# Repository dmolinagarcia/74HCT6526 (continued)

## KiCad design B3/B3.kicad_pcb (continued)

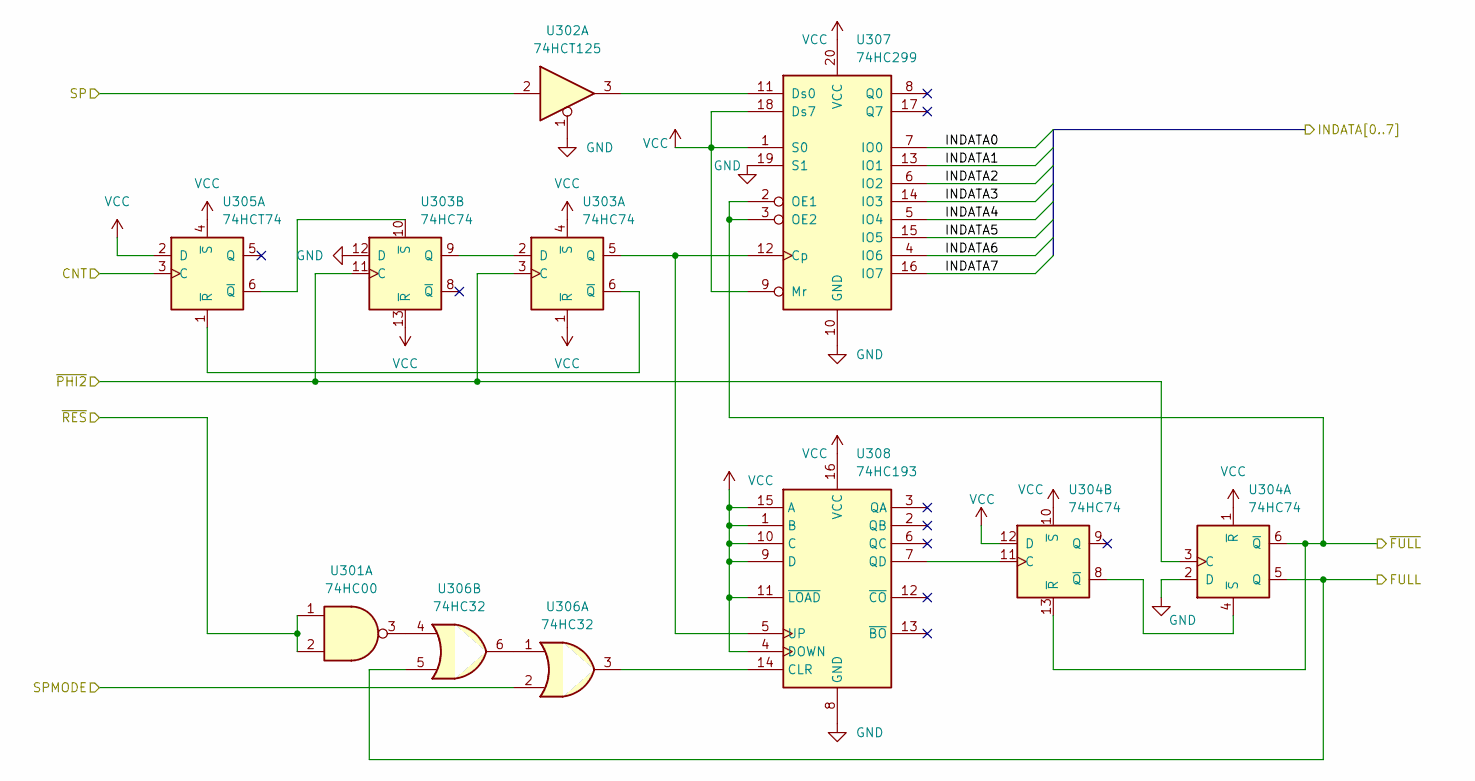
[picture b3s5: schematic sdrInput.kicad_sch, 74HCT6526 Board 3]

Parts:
U301: 74HC00; SO-14_3.9x8.65mm_P1.27mm
U302: 74HCT125; SO-14_3.9x8.65mm_P1.27mm
U303, U304: 74HC74; SO-14_3.9x8.65mm_P1.27mm
U305: 74HCT74; SO-14_3.9x8.65mm_P1.27mm
U306: 74HC32; SO-14_3.9x8.65mm_P1.27mm
U307: 74HC299; SOIC-20W_7.5x12.8mm_P1.27mm
U308: 74HC193; SO-16_3.9x9.9mm_P1.27mm

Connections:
/sdr/sdrController/~FULL: U304.6 (~Q), U304.13 (~R), U307.2 (OE1), U307.3 (OE2); also elsewhere on the board
/sdr/sdrInput/FULL: U304.5 (Q), U306.5; also elsewhere on the board
/sdr/sdrInput/INDATA0: U307.7 (IO0); also elsewhere on the board
/sdr/sdrInput/INDATA1: U307.13 (IO1); also elsewhere on the board
/sdr/sdrInput/INDATA2: U307.6 (IO2); also elsewhere on the board
/sdr/sdrInput/INDATA3: U307.14 (IO3); also elsewhere on the board
/sdr/sdrInput/INDATA4: U307.5 (IO4); also elsewhere on the board
/sdr/sdrInput/INDATA5: U307.15 (IO5); also elsewhere on the board
/sdr/sdrInput/INDATA6: U307.4 (IO6); also elsewhere on the board
/sdr/sdrInput/INDATA7: U307.16 (IO7); also elsewhere on the board
/~PHI2: U303.3 (C), U303.11 (C), U304.3 (C); also elsewhere on the board
CNT: U305.3 (C); also elsewhere on the board
GND: U302.1, U303.12 (D), U304.2 (D), U307.10 (GND), U307.19 (S1), U308.8 (GND); also elsewhere on the board
unnamed: U301.3, U306.4
unnamed: U302.3, U307.11 (Ds0)
unnamed: U303.2 (D), U303.9 (Q)
unnamed: U303.5 (Q), U307.12 (Cp), U308.5 (UP)
unnamed: U303.6 (~Q), U305.1 (~R)
unnamed: U303.10 (~S), U305.6 (~Q)
unnamed: U304.4 (~S), U304.8 (~Q)
unnamed: U304.11 (C), U308.7 (QD)
unnamed: U306.1, U306.6
unnamed: U306.3, U308.14 (CLR)
SP: U302.2; also elsewhere on the board
SPMODE: U306.2; also elsewhere on the board
VCC: U303.1 (~R), U303.4 (~S), U303.13 (~R), U304.1 (~R), U304.10 (~S), U304.12 (D), U305.2 (D), U305.4 (~S), U307.1 (S0), U307.9 (Mr), U307.18 (Ds7), U307.20 (VCC), U308.1 (B), U308.4 (DOWN), U308.9 (D), U308.10 (C), U308.11 (~LOAD), U308.15 (A), U308.16 (VCC); also elsewhere on the board
~RES: U301.1, U301.2; also elsewhere on the board

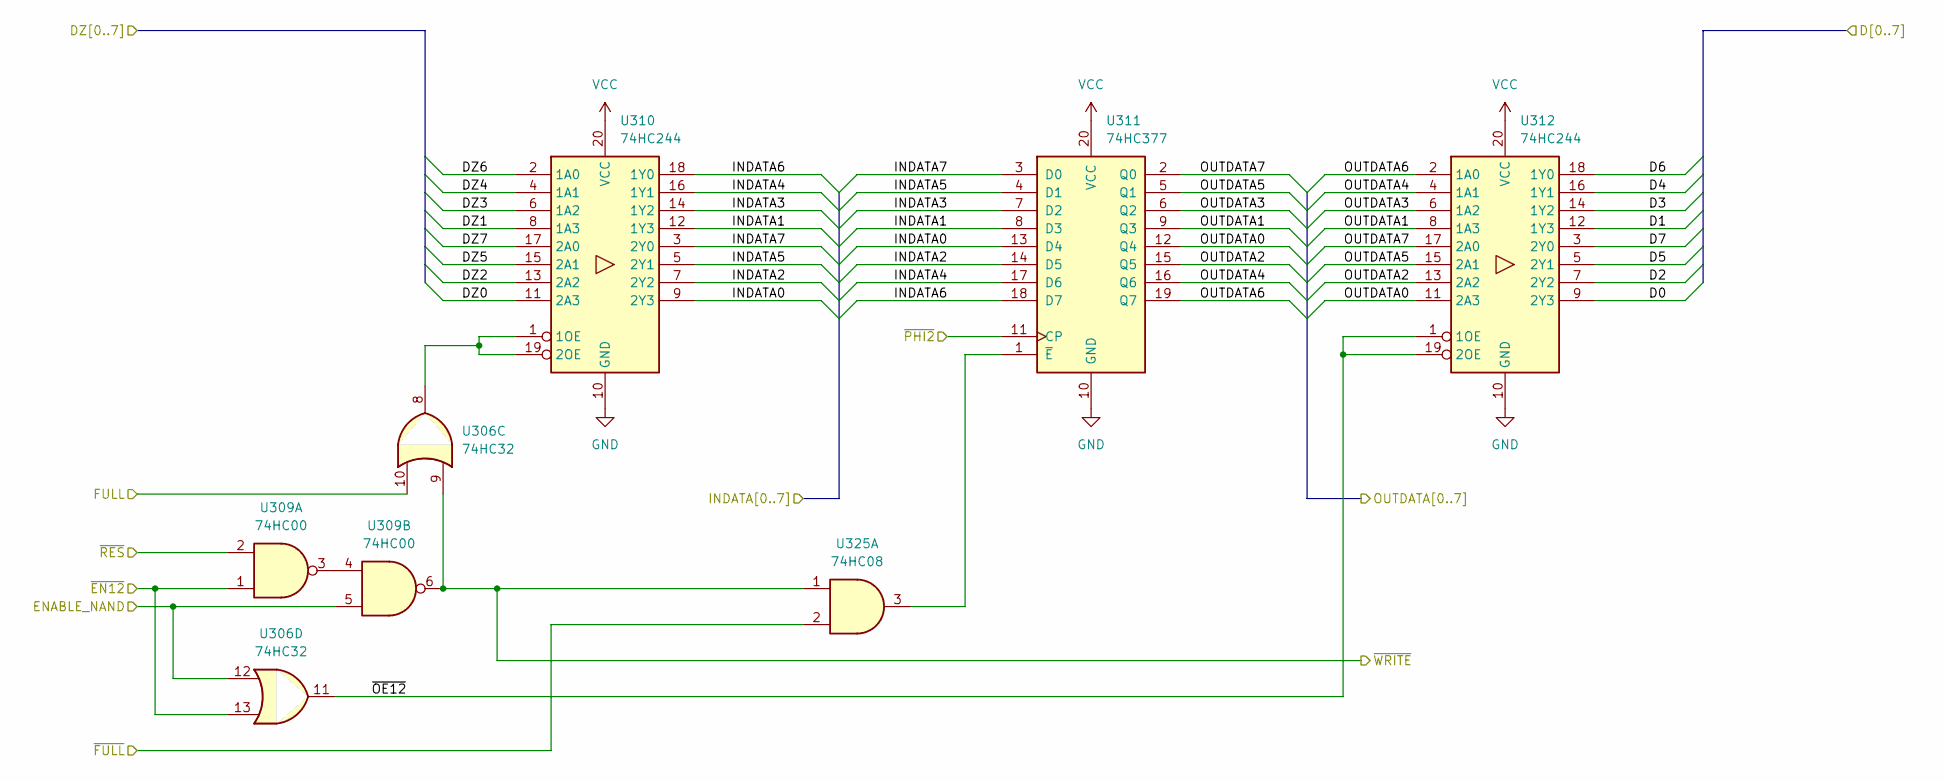
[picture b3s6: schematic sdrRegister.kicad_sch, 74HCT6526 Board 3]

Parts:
U306: 74HC32; SO-14_3.9x8.65mm_P1.27mm
U309: 74HC00; SO-14_3.9x8.65mm_P1.27mm
U310, U312: 74HC244; SOIC-20W_7.5x12.8mm_P1.27mm
U311: 74HC377; SOIC-20W_7.5x12.8mm_P1.27mm
U325: 74HC08; SO-14_3.9x8.65mm_P1.27mm

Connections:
/sdr/sdrController/~FULL: U325.2; also elsewhere on the board
/sdr/sdrController/~WRITE: U306.9, U309.6, U325.1; also elsewhere on the board
/sdr/sdrInput/FULL: U306.10; also elsewhere on the board
/sdr/sdrInput/INDATA0: U310.9 (2Y3), U311.13 (D4); also elsewhere on the board
/sdr/sdrInput/INDATA1: U310.12 (1Y3), U311.8 (D3); also elsewhere on the board
/sdr/sdrInput/INDATA2: U310.7 (2Y2), U311.14 (D5); also elsewhere on the board
/sdr/sdrInput/INDATA3: U310.14 (1Y2), U311.7 (D2); also elsewhere on the board
/sdr/sdrInput/INDATA4: U310.16 (1Y1), U311.17 (D6); also elsewhere on the board
/sdr/sdrInput/INDATA5: U310.5 (2Y1), U311.4 (D1); also elsewhere on the board
/sdr/sdrInput/INDATA6: U310.18 (1Y0), U311.18 (D7); also elsewhere on the board
/sdr/sdrInput/INDATA7: U310.3 (2Y0), U311.3 (D0); also elsewhere on the board
/sdr/sdrOutput/OUTDATA0: U311.12 (Q4), U312.11 (2A3); also elsewhere on the board
/sdr/sdrOutput/OUTDATA1: U311.9 (Q3), U312.8 (1A3); also elsewhere on the board
/sdr/sdrOutput/OUTDATA2: U311.15 (Q5), U312.13 (2A2); also elsewhere on the board
/sdr/sdrOutput/OUTDATA3: U311.6 (Q2), U312.6 (1A2); also elsewhere on the board
/sdr/sdrOutput/OUTDATA4: U311.16 (Q6), U312.4 (1A1); also elsewhere on the board
/sdr/sdrOutput/OUTDATA5: U311.5 (Q1), U312.15 (2A1); also elsewhere on the board
/sdr/sdrOutput/OUTDATA6: U311.19 (Q7), U312.2 (1A0); also elsewhere on the board
/sdr/sdrOutput/OUTDATA7: U311.2 (Q0), U312.17 (2A0); also elsewhere on the board
/sdr/sdrRegister/~OE12: U306.11, U312.1 (1OE), U312.19 (2OE)
/~PHI2: U311.11 (CP); also elsewhere on the board
D0: U312.9 (2Y3); also elsewhere on the board
D1: U312.12 (1Y3); also elsewhere on the board
D2: U312.7 (2Y2); also elsewhere on the board
D3: U312.14 (1Y2); also elsewhere on the board
D4: U312.16 (1Y1); also elsewhere on the board
D5: U312.5 (2Y1); also elsewhere on the board
D6: U312.18 (1Y0); also elsewhere on the board
D7: U312.3 (2Y0); also elsewhere on the board
DZ0: U310.11 (2A3); also elsewhere on the board
DZ1: U310.8 (1A3); also elsewhere on the board
DZ2: U310.13 (2A2); also elsewhere on the board
DZ3: U310.6 (1A2); also elsewhere on the board
DZ4: U310.4 (1A1); also elsewhere on the board
DZ5: U310.15 (2A1); also elsewhere on the board
DZ6: U310.2 (1A0); also elsewhere on the board
DZ7: U310.17 (2A0); also elsewhere on the board
ENABLE_NAND: U306.12, U309.5; also elsewhere on the board
GND: U310.10 (GND), U311.10 (GND), U312.10 (GND); also elsewhere on the board
unnamed: U306.8, U310.1 (1OE), U310.19 (2OE)
unnamed: U309.3, U309.4
unnamed: U311.1 (~E), U325.3
VCC: U310.20 (VCC), U311.20 (VCC), U312.20 (VCC); also elsewhere on the board
~EN12: U306.13, U309.1; also elsewhere on the board
~RES: U309.2; also elsewhere on the board

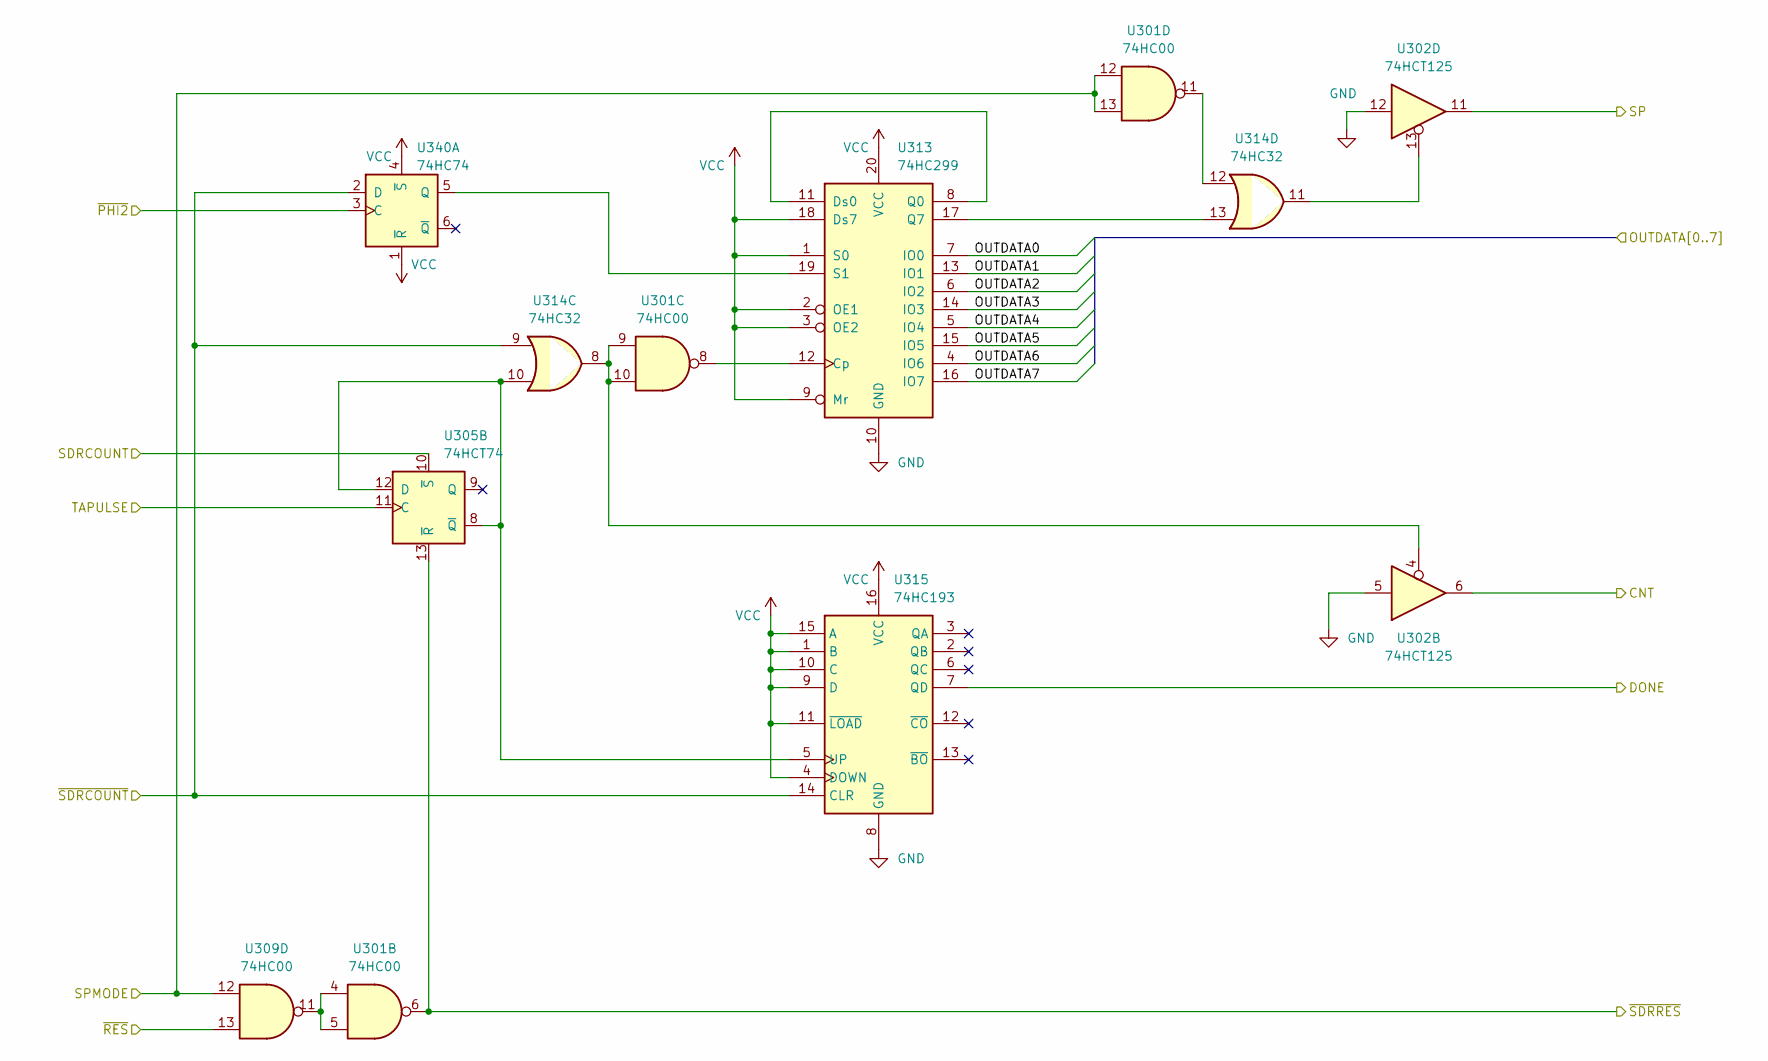
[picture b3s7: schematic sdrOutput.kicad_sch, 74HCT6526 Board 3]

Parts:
U301, U309: 74HC00; SO-14_3.9x8.65mm_P1.27mm
U302: 74HCT125; SO-14_3.9x8.65mm_P1.27mm
U305: 74HCT74; SO-14_3.9x8.65mm_P1.27mm
U313: 74HC299; SOIC-20W_7.5x12.8mm_P1.27mm
U314: 74HC32; SO-14_3.9x8.65mm_P1.27mm
U315: 74HC193; SO-16_3.9x9.9mm_P1.27mm
U340: 74HC74; SO-14_3.9x8.65mm_P1.27mm

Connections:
/sdr/sdrController/DONE: U315.7 (QD); also elsewhere on the board
/sdr/sdrController/SDRCOUNT: U305.10 (~S); also elsewhere on the board
/sdr/sdrController/~SDRCOUNT: U314.9, U315.14 (CLR), U340.2 (D); also elsewhere on the board
/sdr/sdrController/~SDRRES: U301.6, U305.13 (~R); also elsewhere on the board
/sdr/sdrOutput/OUTDATA0: U313.7 (IO0); also elsewhere on the board
/sdr/sdrOutput/OUTDATA1: U313.13 (IO1); also elsewhere on the board
/sdr/sdrOutput/OUTDATA2: U313.6 (IO2); also elsewhere on the board
/sdr/sdrOutput/OUTDATA3: U313.14 (IO3); also elsewhere on the board
/sdr/sdrOutput/OUTDATA4: U313.5 (IO4); also elsewhere on the board
/sdr/sdrOutput/OUTDATA5: U313.15 (IO5); also elsewhere on the board
/sdr/sdrOutput/OUTDATA6: U313.4 (IO6); also elsewhere on the board
/sdr/sdrOutput/OUTDATA7: U313.16 (IO7); also elsewhere on the board
/~PHI2: U340.3 (C); also elsewhere on the board
CNT: U302.6; also elsewhere on the board
GND: U302.5, U302.12, U313.10 (GND), U315.8 (GND); also elsewhere on the board
unnamed: U301.4, U301.5, U309.11
unnamed: U301.8, U313.12 (Cp)
unnamed: U301.9, U301.10, U302.4, U314.8
unnamed: U301.11, U314.12
unnamed: U302.13, U314.11
unnamed: U305.8 (~Q), U305.12 (D), U314.10, U315.5 (UP)
unnamed: U313.8 (Q0), U313.11 (Ds0)
unnamed: U313.17 (Q7), U314.13
unnamed: U313.19 (S1), U340.5 (Q)
SP: U302.11; also elsewhere on the board
SPMODE: U301.12, U301.13, U309.12; also elsewhere on the board
TAPULSE: U305.11 (C); also elsewhere on the board
VCC: U313.1 (S0), U313.2 (OE1), U313.3 (OE2), U313.9 (Mr), U313.18 (Ds7), U313.20 (VCC), U315.1 (B), U315.4 (DOWN), U315.9 (D), U315.10 (C), U315.11 (~LOAD), U315.15 (A), U315.16 (VCC), U340.1 (~R), U340.4 (~S); also elsewhere on the board
~RES: U309.13; also elsewhere on the board

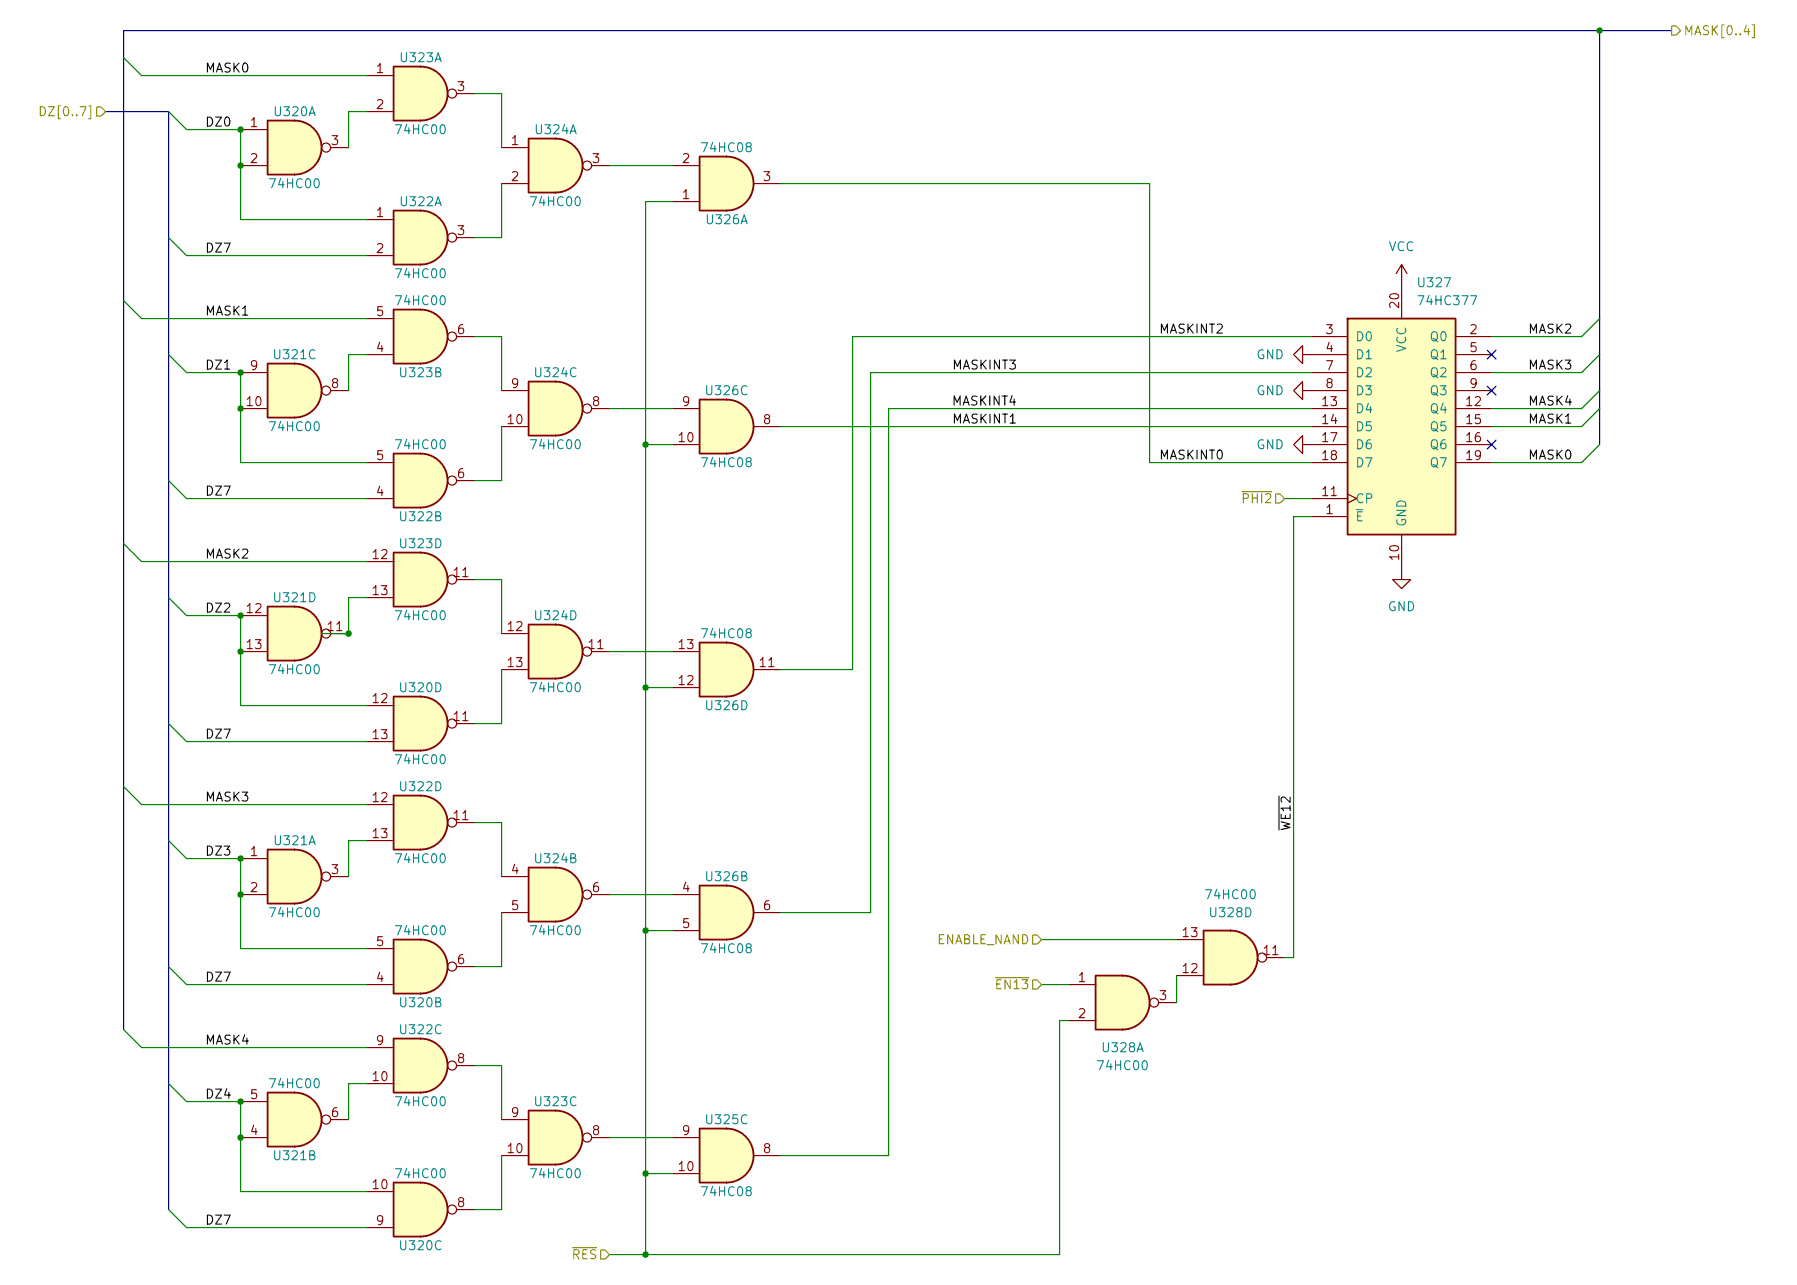
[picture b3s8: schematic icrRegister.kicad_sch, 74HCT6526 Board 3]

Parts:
U320, U321, U322, U323, U324, U328: 74HC00; SO-14_3.9x8.65mm_P1.27mm
U325, U326: 74HC08; SO-14_3.9x8.65mm_P1.27mm
U327: 74HC377; SOIC-20W_7.5x12.8mm_P1.27mm

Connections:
/icr/icrControl/MASK0: U323.1, U327.19 (Q7); also elsewhere on the board
/icr/icrControl/MASK1: U323.5, U327.15 (Q5); also elsewhere on the board
/icr/icrControl/MASK2: U323.12, U327.2 (Q0); also elsewhere on the board
/icr/icrControl/MASK3: U322.12, U327.6 (Q2); also elsewhere on the board
/icr/icrControl/MASK4: U322.9, U327.12 (Q4); also elsewhere on the board
/icr/icrRegister/MASKINT0: U326.3, U327.18 (D7)
/icr/icrRegister/MASKINT1: U326.8, U327.14 (D5)
/icr/icrRegister/MASKINT2: U326.11, U327.3 (D0)
/icr/icrRegister/MASKINT3: U326.6, U327.7 (D2)
/icr/icrRegister/MASKINT4: U325.8, U327.13 (D4)
/icr/icrRegister/~WE12: U327.1 (~E), U328.11
/~PHI2: U327.11 (CP); also elsewhere on the board
DZ0: U320.1, U320.2, U322.1; also elsewhere on the board
DZ1: U321.9, U321.10, U322.5; also elsewhere on the board
DZ2: U320.12, U321.12, U321.13; also elsewhere on the board
DZ3: U320.5, U321.1, U321.2; also elsewhere on the board
DZ4: U320.10, U321.4, U321.5; also elsewhere on the board
DZ7: U320.4, U320.9, U320.13, U322.2, U322.4; also elsewhere on the board
ENABLE_NAND: U328.13; also elsewhere on the board
GND: U327.4 (D1), U327.8 (D3), U327.10 (GND), U327.17 (D6); also elsewhere on the board
unnamed: U320.3, U323.2
unnamed: U320.6, U324.5
unnamed: U320.8, U323.10
unnamed: U320.11, U324.13
unnamed: U321.3, U322.13
unnamed: U321.6, U322.10
unnamed: U321.8, U323.4
unnamed: U321.11, U323.13
unnamed: U322.3, U324.2
unnamed: U322.6, U324.10
unnamed: U322.8, U323.9
unnamed: U322.11, U324.4
unnamed: U323.3, U324.1
unnamed: U323.6, U324.9
unnamed: U323.8, U325.9
unnamed: U323.11, U324.12
unnamed: U324.3, U326.2
unnamed: U324.6, U326.4
unnamed: U324.8, U326.9
unnamed: U324.11, U326.13
unnamed: U328.3, U328.12
VCC: U327.20 (VCC); also elsewhere on the board
~EN13: U328.1; also elsewhere on the board
~RES: U325.10, U326.1, U326.5, U326.10, U326.12, U328.2; also elsewhere on the board

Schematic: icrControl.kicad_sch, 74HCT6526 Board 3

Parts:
SW301: SW_SPDT; SW_SPDT_PCM12
U329: 74HC00; SO-14_3.9x8.65mm_P1.27mm
U330, U331, U332, U333, U334, U342: 74HC74; SO-14_3.9x8.65mm_P1.27mm
U335: 74HCT04; SO-14_3.9x8.65mm_P1.27mm
U336: 74HC244; SOIC-20W_7.5x12.8mm_P1.27mm
U337, U339: 74HC08; SO-14_3.9x8.65mm_P1.27mm
U338: 74HC32; SO-14_3.9x8.65mm_P1.27mm
U341: 74HC157; SO-16_3.9x9.9mm_P1.27mm

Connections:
/icr/icrControl/ICR0: U331.5 (Q), U336.2 (1A0), U339.12
/icr/icrControl/ICR1: U332.9 (Q), U336.17 (2A0)
/icr/icrControl/ICR2: U332.5 (Q), U336.4 (1A1), U337.4
/icr/icrControl/ICR3: U331.9 (Q), U336.15 (2A1), U337.9
/icr/icrControl/ICR4: U333.9 (Q), U336.13 (2A2), U339.9
/icr/icrControl/ICR7: U336.8 (1A3), U341.7
/icr/icrControl/ICRCLR: U329.6, U330.12 (D)
/icr/icrControl/MASK0: U339.13; also elsewhere on the board
/icr/icrControl/MASK1: U337.13; also elsewhere on the board
/icr/icrControl/MASK2: U337.5; also elsewhere on the board
/icr/icrControl/MASK3: U337.10; also elsewhere on the board
/icr/icrControl/MASK4: U339.10; also elsewhere on the board
/icr/icrControl/~ICRCLR1: U330.8 (~Q), U331.1 (~R), U331.13 (~R), U332.1 (~R), U333.13 (~R), U334.1 (~R), U334.13 (~R), U341.2, U342.1 (~R), U342.13 (~R)
/icr/icrControl/~ICRCLR2: U330.6 (~Q), U341.3
/icr/icrControl/~OE13: U329.5, U329.8, U336.1 (1OE), U336.19 (2OE)
/~PHI2: U330.3 (C), U330.11 (C), U334.11 (C), U342.11 (C); also elsewhere on the board
/~SDRIRQ: U331.10 (~S); also elsewhere on the board
D0: U336.18 (1Y0); also elsewhere on the board
D1: U336.3 (2Y0); also elsewhere on the board
D2: U336.16 (1Y1); also elsewhere on the board
D3: U336.5 (2Y1); also elsewhere on the board
D4: U336.7 (2Y2); also elsewhere on the board
D5: U336.14 (1Y2); also elsewhere on the board
D6: U336.9 (2Y3); also elsewhere on the board
D7: U336.12 (1Y3); also elsewhere on the board
ENABLE_NAND: U329.12, U329.13; also elsewhere on the board
GND: SW301.1 (A), U336.6 (1A2), U336.10 (GND), U336.11 (2A3), U341.15 (~E); also elsewhere on the board
unnamed: SW301.2 (B), U341.1 (S)
unnamed: U329.3, U329.9
unnamed: U329.10, U329.11
unnamed: U330.2 (D), U330.9 (Q)
unnamed: U331.4 (~S), U335.10
unnamed: U332.4 (~S), U335.2
unnamed: U332.10 (~S), U335.12
unnamed: U332.13 (~R), U341.4
unnamed: U333.1 (~R), U333.8 (~Q)
unnamed: U333.3 (C), U335.4
unnamed: U333.6 (~Q), U333.10 (~S)
unnamed: U334.4 (~S), U335.8, U342.4 (~S)
unnamed: U334.9 (Q), U341.6
unnamed: U334.5 (Q), U334.12 (D), U341.5
unnamed: U335.9, U338.6
unnamed: U337.6, U338.12
unnamed: U337.8, U338.13
unnamed: U337.11, U338.2
unnamed: U338.1, U339.11
unnamed: U338.3, U338.9
unnamed: U338.4, U338.8
unnamed: U338.5, U339.8
unnamed: U338.10, U338.11
unnamed: U341.10, U342.8 (~Q)
unnamed: U341.11, U342.6 (~Q)
unnamed: U342.5 (Q), U342.12 (D)
TAPULSE: U335.11; also elsewhere on the board
TBPULSE: U335.13, U337.12; also elsewhere on the board
TODIRQ: U335.1; also elsewhere on the board
VCC: SW301.3 (C), U330.1 (~R), U330.4 (~S), U330.10 (~S), U330.13 (~R), U331.2 (D), U331.3 (C), U331.11 (C), U331.12 (D), U332.2 (D), U332.3 (C), U332.11 (C), U332.12 (D), U333.2 (D), U333.4 (~S), U333.11 (C), U333.12 (D), U334.2 (D), U334.3 (C), U334.10 (~S), U336.20 (VCC), U342.2 (D), U342.3 (C), U342.10 (~S); also elsewhere on the board
~EN13: U329.1, U329.2; also elsewhere on the board
~FLAG: U335.3; also elsewhere on the board
~IRQ: U341.9; also elsewhere on the board
~RES: U329.4; also elsewhere on the board

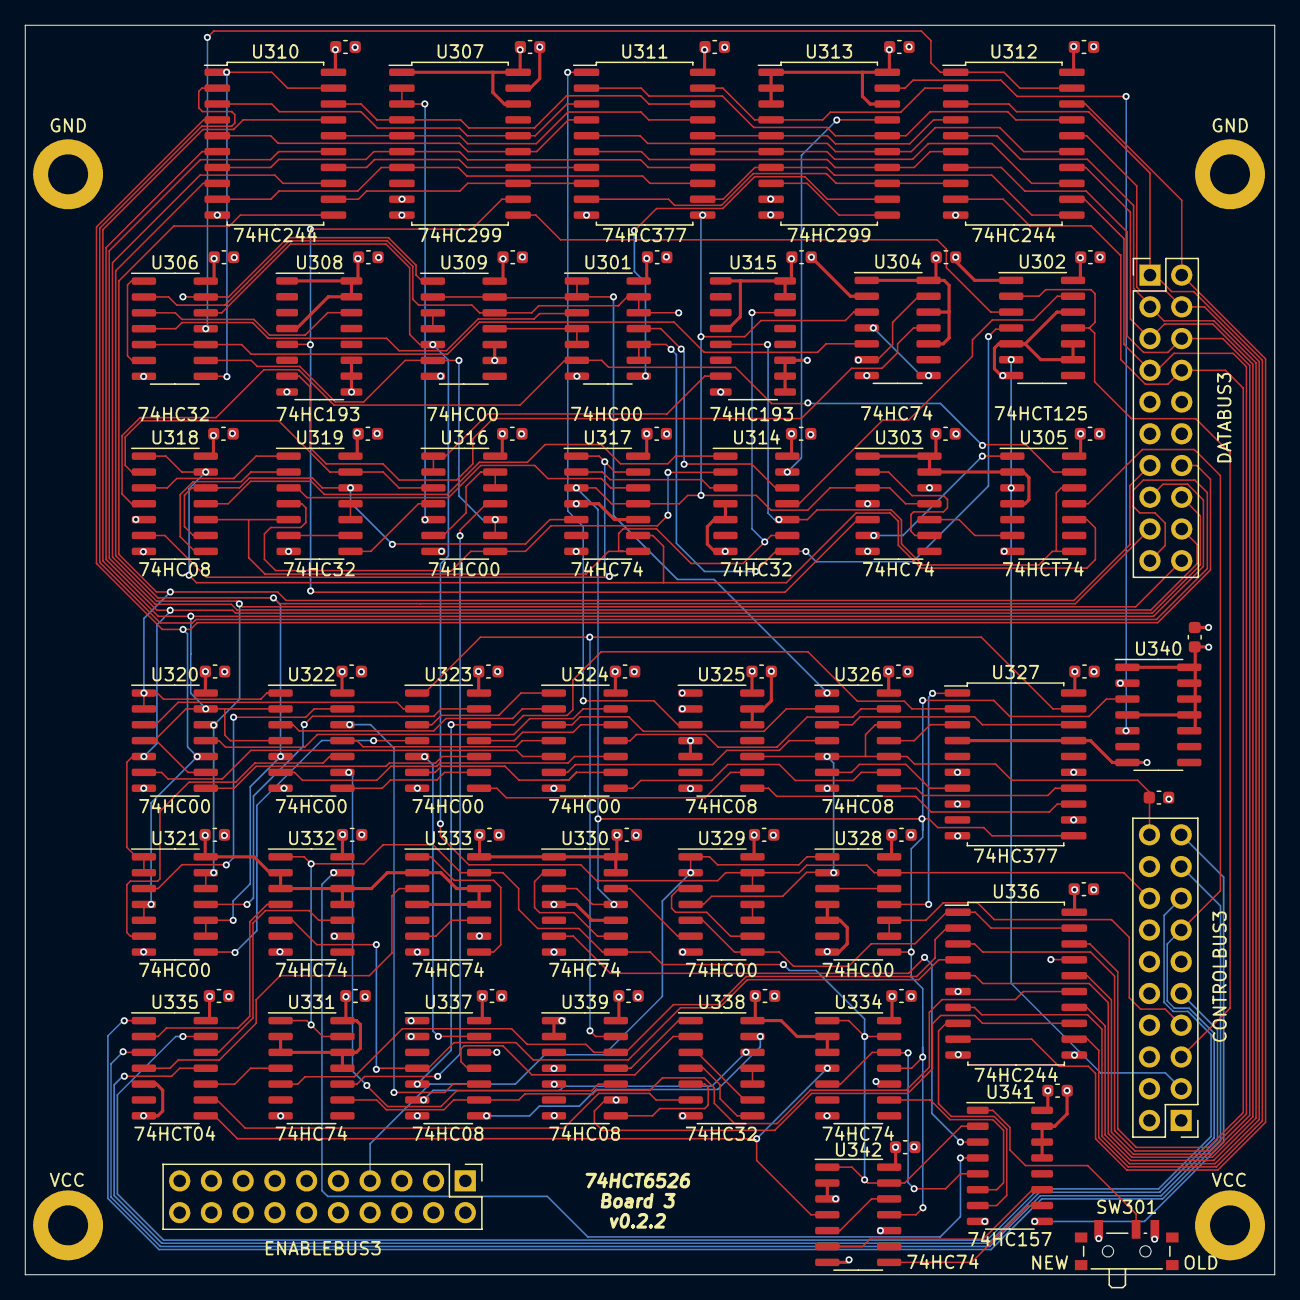
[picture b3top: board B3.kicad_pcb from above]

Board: 4 copper layers, 100.0 x 100.0 mm, 93 parts (0 on the bottom side), 161 nets.

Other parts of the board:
GND101, GND102: GND; MountingHole_2.2mm_M2_DIN965_Pad
VCC101, VCC102: VCC; MountingHole_2.2mm_M2_DIN965_Pad

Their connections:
GND: GND101.GND, GND102.GND; also elsewhere on the board
VCC: VCC101.VCC, VCC102.VCC; also elsewhere on the board

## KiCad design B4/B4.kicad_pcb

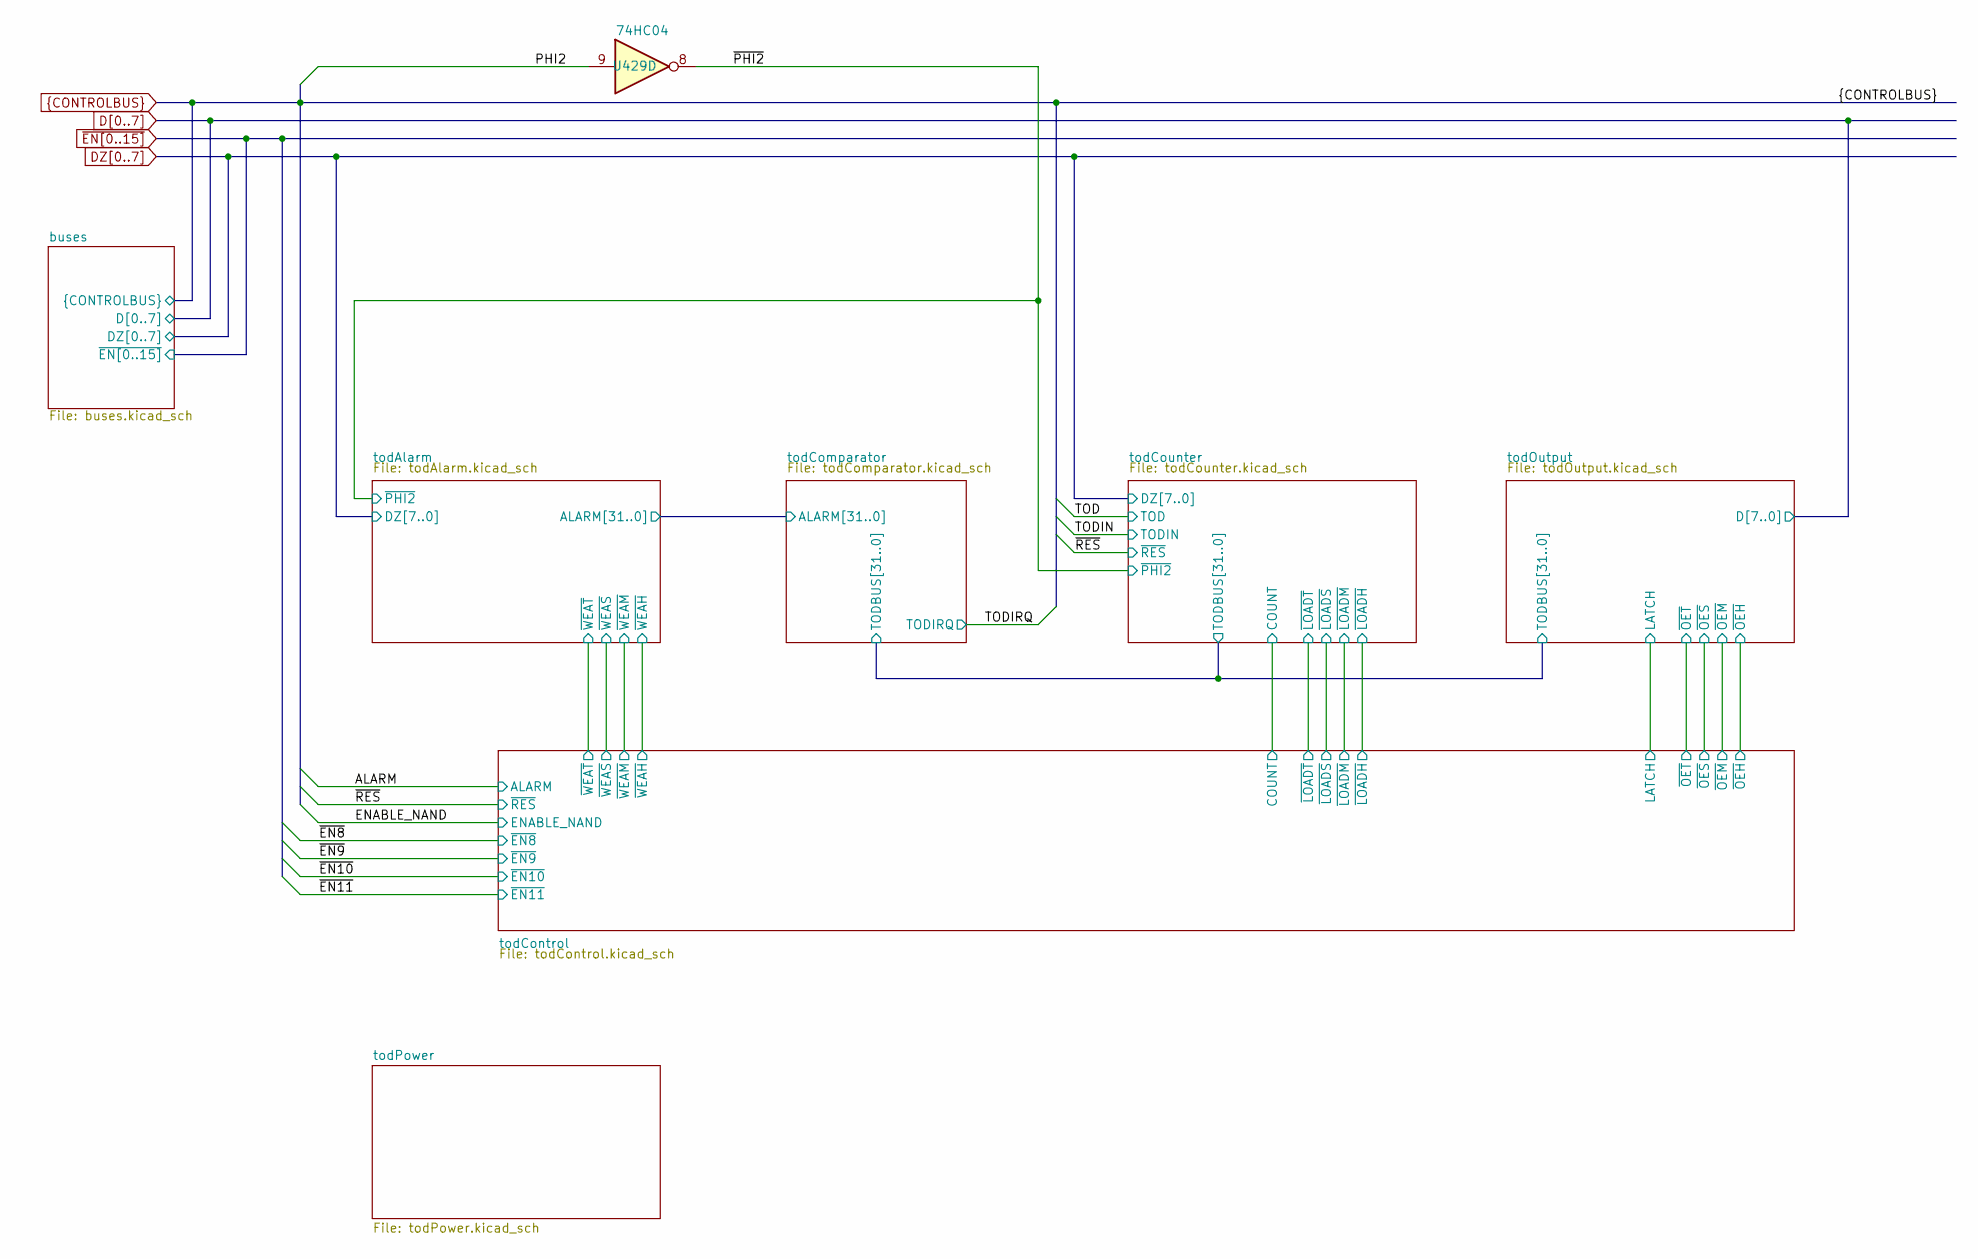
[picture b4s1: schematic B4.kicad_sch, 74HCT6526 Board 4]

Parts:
U429: 74HC04; SOIC-14_3.9x8.7mm_P1.27mm

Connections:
/~PHI2: U429.8; also elsewhere on the board
PHI2: U429.9; also elsewhere on the board

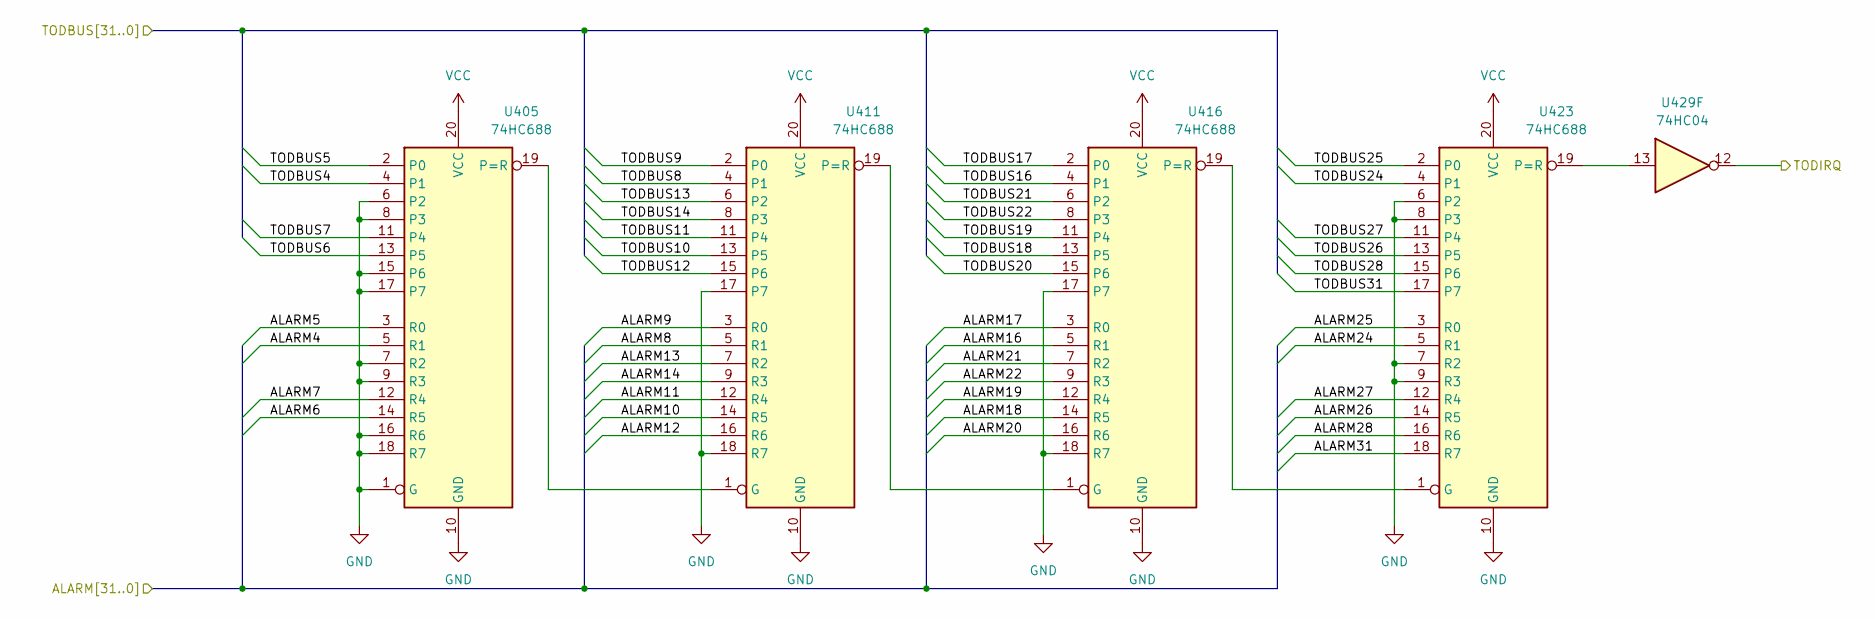
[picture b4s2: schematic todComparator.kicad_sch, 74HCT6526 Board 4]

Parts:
U405, U411, U416, U423: 74HC688; SOIC-20W_7.5x12.8mm_P1.27mm
U429: 74HC04; SOIC-14_3.9x8.7mm_P1.27mm

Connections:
/todAlarm/ALARM4: U405.5 (R1); also elsewhere on the board
/todAlarm/ALARM5: U405.3 (R0); also elsewhere on the board
/todAlarm/ALARM6: U405.14 (R5); also elsewhere on the board
/todAlarm/ALARM7: U405.12 (R4); also elsewhere on the board
/todAlarm/ALARM8: U411.5 (R1); also elsewhere on the board
/todAlarm/ALARM9: U411.3 (R0); also elsewhere on the board
/todAlarm/ALARM10: U411.14 (R5); also elsewhere on the board
/todAlarm/ALARM11: U411.12 (R4); also elsewhere on the board
/todAlarm/ALARM12: U411.16 (R6); also elsewhere on the board
/todAlarm/ALARM13: U411.7 (R2); also elsewhere on the board
/todAlarm/ALARM14: U411.9 (R3); also elsewhere on the board
/todAlarm/ALARM16: U416.5 (R1); also elsewhere on the board
/todAlarm/ALARM17: U416.3 (R0); also elsewhere on the board
/todAlarm/ALARM18: U416.14 (R5); also elsewhere on the board
/todAlarm/ALARM19: U416.12 (R4); also elsewhere on the board
/todAlarm/ALARM20: U416.16 (R6); also elsewhere on the board
/todAlarm/ALARM21: U416.7 (R2); also elsewhere on the board
/todAlarm/ALARM22: U416.9 (R3); also elsewhere on the board
/todAlarm/ALARM24: U423.5 (R1); also elsewhere on the board
/todAlarm/ALARM25: U423.3 (R0); also elsewhere on the board
/todAlarm/ALARM26: U423.14 (R5); also elsewhere on the board
/todAlarm/ALARM27: U423.12 (R4); also elsewhere on the board
/todAlarm/ALARM28: U423.16 (R6); also elsewhere on the board
/todAlarm/ALARM31: U423.18 (R7); also elsewhere on the board
/todComparator/TODBUS4: U405.4 (P1); also elsewhere on the board
/todComparator/TODBUS5: U405.2 (P0); also elsewhere on the board
/todComparator/TODBUS6: U405.13 (P5); also elsewhere on the board
/todComparator/TODBUS7: U405.11 (P4); also elsewhere on the board
/todComparator/TODBUS8: U411.4 (P1); also elsewhere on the board
/todComparator/TODBUS9: U411.2 (P0); also elsewhere on the board
/todComparator/TODBUS10: U411.13 (P5); also elsewhere on the board
/todComparator/TODBUS11: U411.11 (P4); also elsewhere on the board
/todComparator/TODBUS12: U411.15 (P6); also elsewhere on the board
/todComparator/TODBUS13: U411.6 (P2); also elsewhere on the board
/todComparator/TODBUS14: U411.8 (P3); also elsewhere on the board
/todComparator/TODBUS16: U416.4 (P1); also elsewhere on the board
/todComparator/TODBUS17: U416.2 (P0); also elsewhere on the board
/todComparator/TODBUS18: U416.13 (P5); also elsewhere on the board
/todComparator/TODBUS19: U416.11 (P4); also elsewhere on the board
/todComparator/TODBUS20: U416.15 (P6); also elsewhere on the board
/todComparator/TODBUS21: U416.6 (P2); also elsewhere on the board
/todComparator/TODBUS22: U416.8 (P3); also elsewhere on the board
/todComparator/TODBUS24: U423.4 (P1); also elsewhere on the board
/todComparator/TODBUS25: U423.2 (P0); also elsewhere on the board
/todComparator/TODBUS26: U423.13 (P5); also elsewhere on the board
/todComparator/TODBUS27: U423.11 (P4); also elsewhere on the board
/todComparator/TODBUS28: U423.15 (P6); also elsewhere on the board
/todComparator/TODBUS31: U423.17 (P7); also elsewhere on the board
GND: U405.1 (G), U405.6 (P2), U405.7 (R2), U405.8 (P3), U405.9 (R3), U405.10 (GND), U405.15 (P6), U405.16 (R6), U405.17 (P7), U405.18 (R7), U411.10 (GND), U411.17 (P7), U411.18 (R7), U416.10 (GND), U416.17 (P7), U416.18 (R7), U423.6 (P2), U423.7 (R2), U423.8 (P3), U423.9 (R3), U423.10 (GND); also elsewhere on the board
unnamed: U405.19 (P=R), U411.1 (G)
unnamed: U411.19 (P=R), U416.1 (G)
unnamed: U416.19 (P=R), U423.1 (G)
unnamed: U423.19 (P=R), U429.13
TODIRQ: U429.12; also elsewhere on the board
VCC: U405.20 (VCC), U411.20 (VCC), U416.20 (VCC), U423.20 (VCC); also elsewhere on the board
